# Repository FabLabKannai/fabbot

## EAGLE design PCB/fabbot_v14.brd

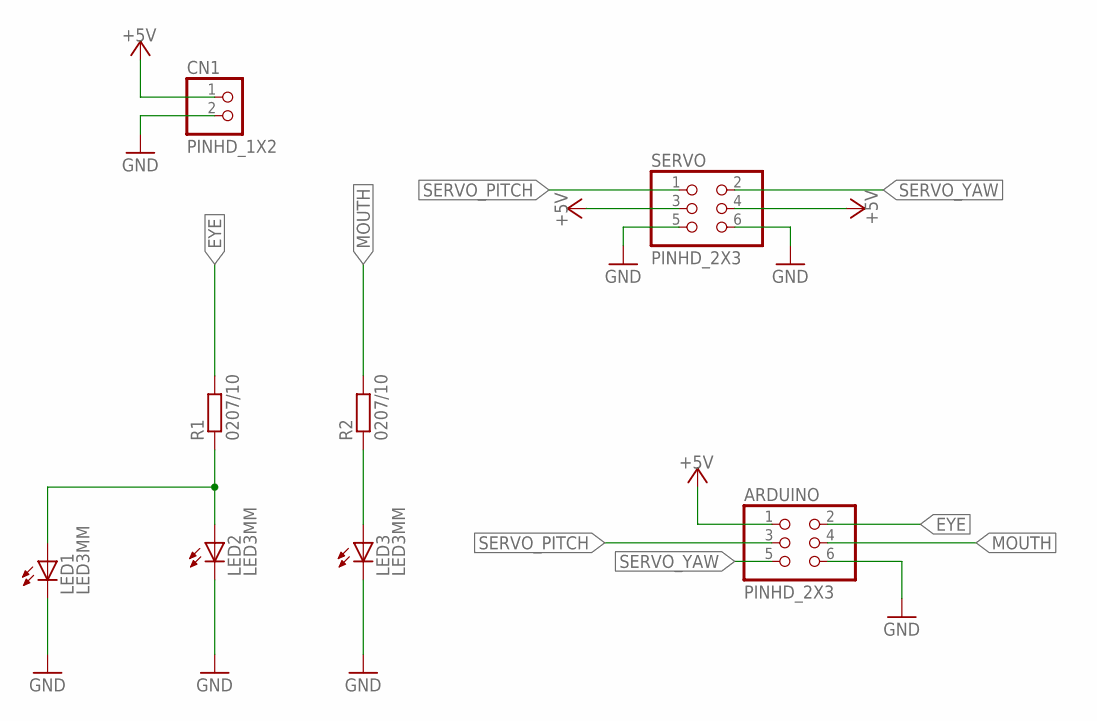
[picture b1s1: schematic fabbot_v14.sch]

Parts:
ARDUINO: PINHD_2X3; 2X03/90
CN1: PINHD_1X2; PINHEAD1X2
LED1, LED2, LED3: LED3MM
R1, R2: 0207/10
SERVO: PINHD_2X3; 2X03/90

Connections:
+5V: ARDUINO.1, CN1.1, SERVO.3, SERVO.4
EYE: ARDUINO.2, R1.2
GND: ARDUINO.6, CN1.2, LED1.K (C), LED2.K (C), LED3.K (C), SERVO.5, SERVO.6
MOUTH: ARDUINO.4, R2.2
unnamed: LED1.A, LED2.A, R1.1
unnamed: LED3.A, R2.1
SERVO_PITCH: ARDUINO.3, SERVO.1
SERVO_YAW: ARDUINO.5, SERVO.2

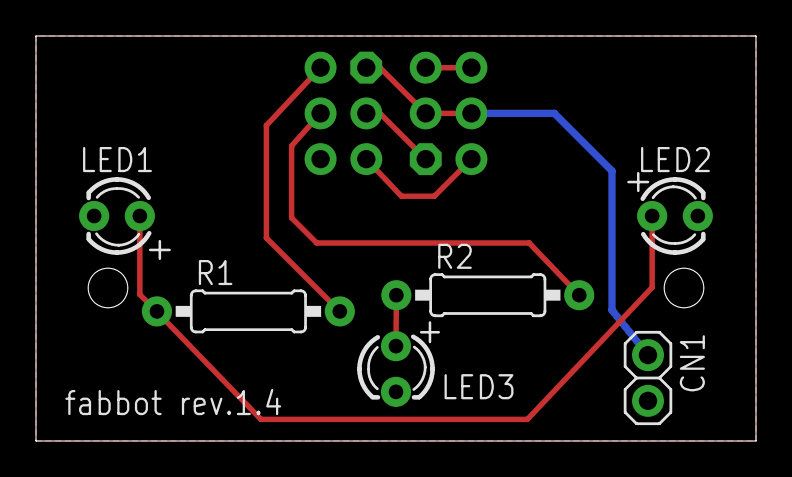
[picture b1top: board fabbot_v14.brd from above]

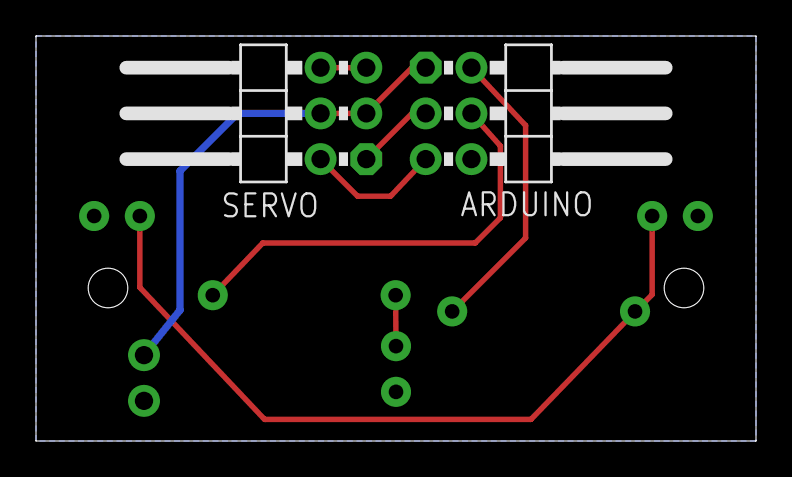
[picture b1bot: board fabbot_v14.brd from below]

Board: 2 copper layers, 40.0 x 22.5 mm, 8 parts (2 on the bottom side), 8 nets.

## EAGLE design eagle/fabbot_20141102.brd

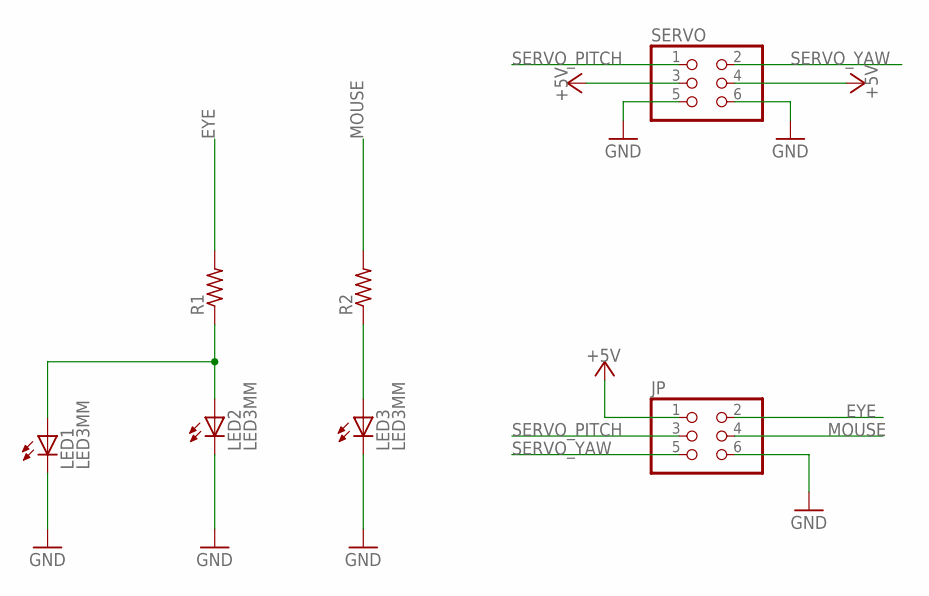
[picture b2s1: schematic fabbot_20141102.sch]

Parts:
JP: PINHD-2X3/90; 2X03/90
LED1, LED2, LED3: LED3MM
R1, R2: R-US_0207/10; 0207/10
SERVO: PINHD-2X3/90; 2X03/90

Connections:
+5V: JP.1, SERVO.3, SERVO.4
EYE: JP.2, R1.2
GND: JP.6, LED1.K (C), LED2.K (C), LED3.K (C), SERVO.5, SERVO.6
MOUSE: JP.4, R2.2
unnamed: LED1.A, LED2.A, R1.1
unnamed: LED3.A, R2.1
SERVO_PITCH: JP.3, SERVO.1
SERVO_YAW: JP.5, SERVO.2

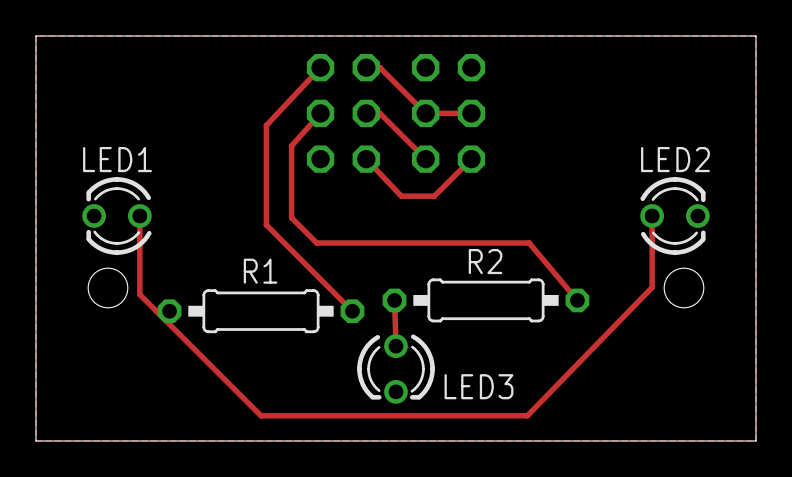
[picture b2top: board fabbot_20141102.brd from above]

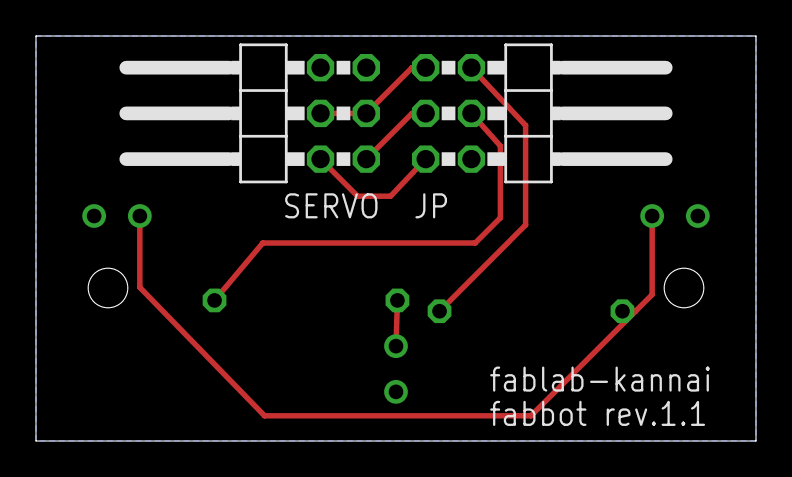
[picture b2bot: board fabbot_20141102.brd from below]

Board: 2 copper layers, 40.0 x 22.5 mm, 7 parts (2 on the bottom side), 8 nets.

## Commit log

2014-11-28 first version
2014-12-09 comments added
2014-12-26 for precise 3Dprinting
2015-01-17 place guide added
2015-01-17 place guide modified
2015-02-02 manual updated
2015-05-09 +raspi version
2015-09-16 renew
2015-09-20 forFLA
2015-09-20 raspi version
2015-10-07 create old version directory
2015-10-07 create old_version directory
2015-10-07 add manual_v5
2015-10-09 update manual
2015-11-16 update eagle data
